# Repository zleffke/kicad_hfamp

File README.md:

# kicad_hfamp
Various KiCAD designs for HF Power Amplifiers

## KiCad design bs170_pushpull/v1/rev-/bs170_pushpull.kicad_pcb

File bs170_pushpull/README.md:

# bs170_pushpull

## Version 1
* Simple BS170 pushpull design
* utilizes two SMT BS170s, but added through hole pads for TO-92 testing.
* utilizes minicircuits baluns...ADTXXXXXX version
    * attempting to achieve wideband 'no tune' design.
    * not yet sure which impedance ratio to use
    * overlaid with through hole in order to test other baluns (hand made wirewound binocular...)
* No actual biasing circuit...planning to test offboard bias circuits.  Did include simple potentiometer based bias.
* Trying to achieve some amount of gain with a 5V drain voltage, most designs use 12V...
* Rev- design intended to test various configurations for biasing and to measure S-parameters.

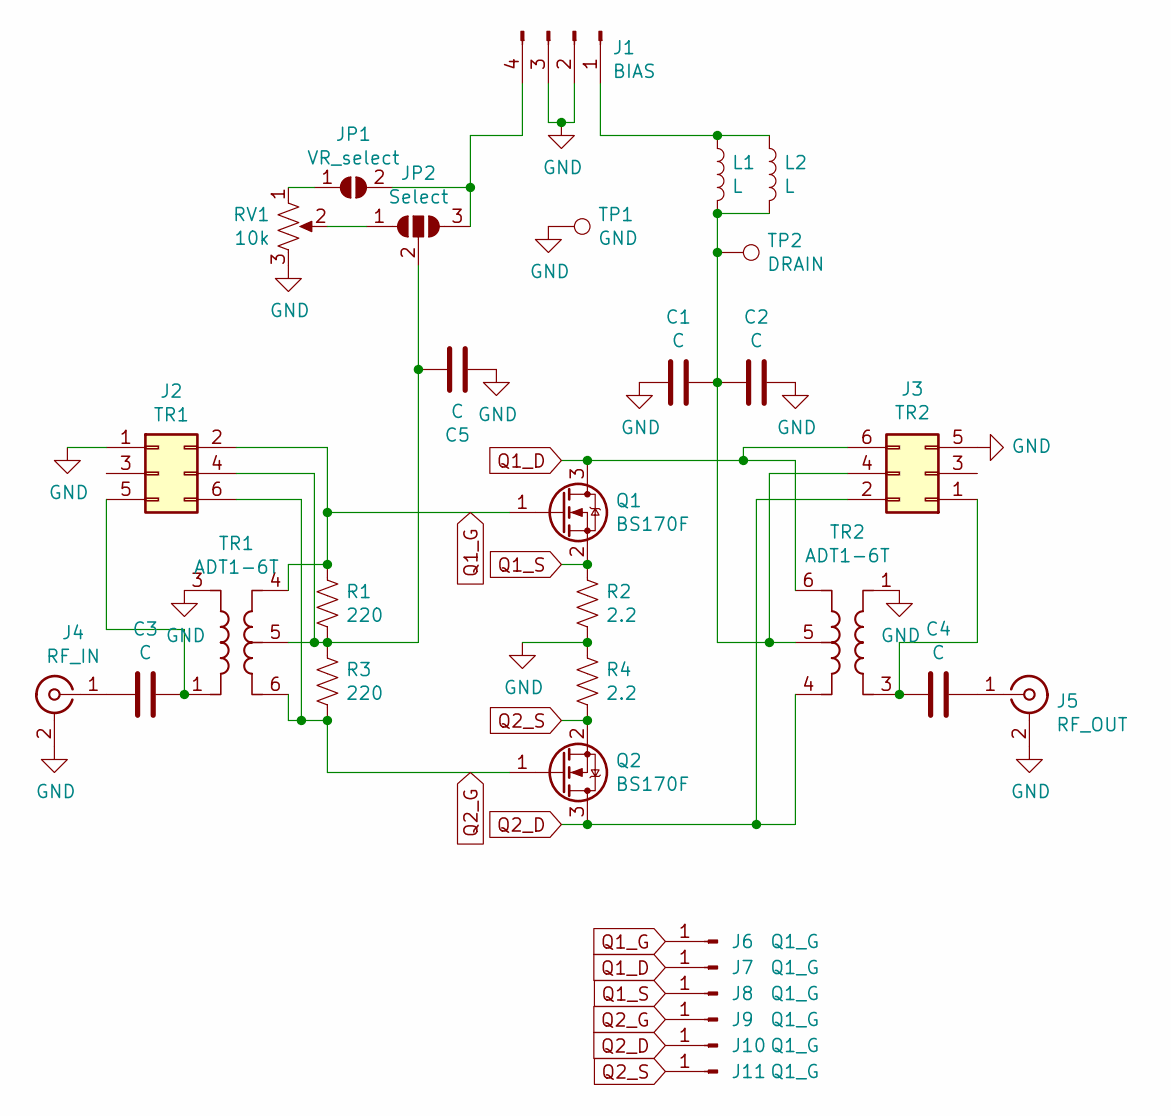
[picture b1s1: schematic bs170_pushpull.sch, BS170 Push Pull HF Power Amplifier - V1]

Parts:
C1, C2, C3, C4, C5: C; 0805
J1: BIAS; PinHeader_1x04_P2.54mm_Vertical
J2: TR1; PinHeader_2x03_P2.54mm_Vertical
J3: TR2; PinHeader_2x03_P2.54mm_Vertical
J4: RF_IN; SMA_Samtec_SMA-J-P-X-ST-EM1_EdgeMount
J5: RF_OUT; SMA_Samtec_SMA-J-P-X-ST-EM1_EdgeMount
J6, J7, J8, J9, J10, J11: Q1_G; PinHeader_1x01_P1.00mm_Vertical
JP1: VR_select; SolderJumper-2_P1.3mm_Open_RoundedPad1.0x1.5mm
JP2: Select; SolderJumper-3_P1.3mm_Open_RoundedPad1.0x1.5mm_NumberLabels
L1: L; PinHeader_1x02_P2.54mm_Vertical
L2: L; 0805
Q1, Q2: BS170F; SOT-23
R1, R3: 220; 0805
R2, R4: 2.2; 0805
RV1: 10k; Potentiometer_Bourns_3314G_Vertical
TP1: GND; TestPoint_Pad_D1.0mm
TP2: DRAIN; TestPoint_Pad_D1.0mm
TR1, TR2: ADT1-6T; Mini-Circuits_CD637_H5.23mm

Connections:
GND: C1.2, C2.1, C5.2, J1.2, J1.3, J2.1, J3.5, J4.2 (Ext), J5.2 (Ext), R2.2, R4.1, RV1.3, TP1.1, TR1.3, TR2.1
unnamed: C1.1, C2.2, J3.4, L1.2, L2.2, TP2.1, TR2.5
unnamed: C3.1, J2.5, TR1.1
unnamed: C3.2, J4.1 (In)
unnamed: C4.1, J5.1 (In)
unnamed: C4.2, J3.1, TR2.3
unnamed: C5.1, J2.4, JP2.2 (C), R1.2, R3.1, TR1.5
unnamed: J1.1, L1.1, L2.1
unnamed: J1.4, JP1.2 (B), JP2.3 (B)
unnamed: JP1.1 (A), RV1.1
unnamed: JP2.1 (A), RV1.2
Q1_D: J3.6, J7.1, Q1.3 (D), TR2.6
Q1_G: J2.2, J6.1, Q1.1 (G), R1.1, TR1.4
Q1_S: J8.1, Q1.2 (S), R2.1
Q2_D: J3.2, J10.1, Q2.3 (D), TR2.4
Q2_G: J2.6, J9.1, Q2.1 (G), R3.2, TR1.6
Q2_S: J11.1, Q2.2 (S), R4.2

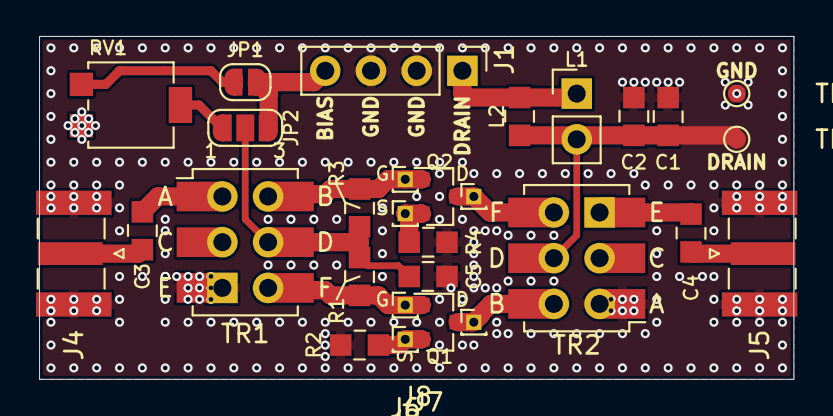
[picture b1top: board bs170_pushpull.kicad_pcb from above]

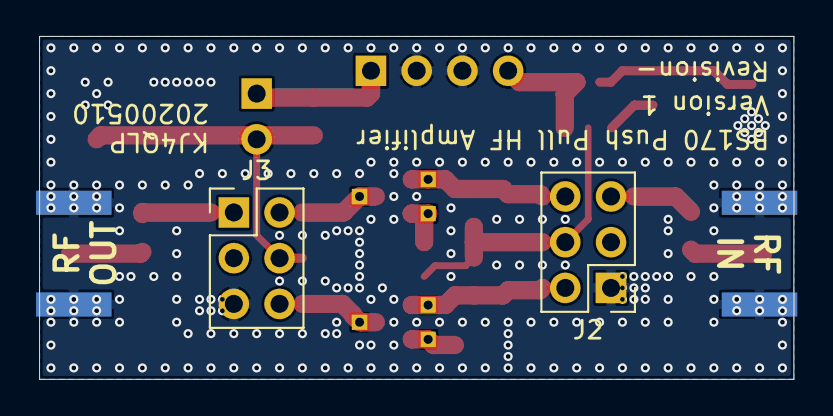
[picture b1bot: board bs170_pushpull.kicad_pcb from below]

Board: 2 copper layers, 41.9 x 19.0 mm, 31 parts (2 on the bottom side), 17 nets.

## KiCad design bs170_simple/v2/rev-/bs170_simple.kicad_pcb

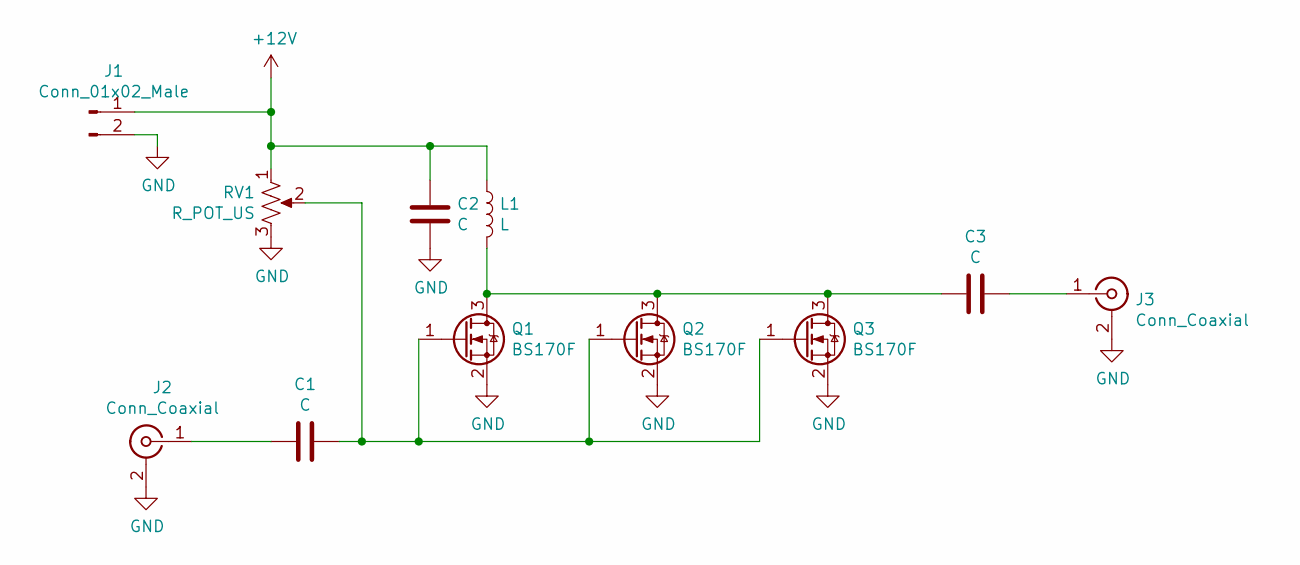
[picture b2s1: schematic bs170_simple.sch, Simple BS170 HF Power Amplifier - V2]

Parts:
C1, C2, C3: C; 0805
J1: Conn_01x02_Male; PinHeader_1x02_P2.54mm_Vertical
J2, J3: Conn_Coaxial; SMA_Samtec_SMA-J-P-X-ST-EM1_EdgeMount
L1: L; 0805
Q1, Q2, Q3: BS170F; SOT-23
RV1: R_POT_US; Potentiometer_Bourns_3314R-GM5_Vertical

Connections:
+12V: C2.2, J1.1, L1.1, RV1.1
GND: C2.1, J1.2, J2.2 (Ext), J3.2 (Ext), Q1.2 (S), Q2.2 (S), Q3.2 (S), RV1.3
unnamed: C1.1, Q1.1 (G), Q2.1 (G), Q3.1 (G), RV1.2
unnamed: C1.2, J2.1 (In)
unnamed: C3.1, J3.1 (In)
unnamed: C3.2, L1.2, Q1.3 (D), Q2.3 (D), Q3.3 (D)

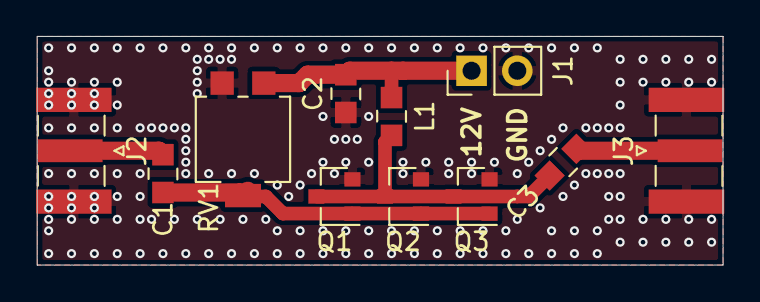
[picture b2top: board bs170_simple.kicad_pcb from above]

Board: 2 copper layers, 38.1 x 12.7 mm, 11 parts (0 on the bottom side), 6 nets.

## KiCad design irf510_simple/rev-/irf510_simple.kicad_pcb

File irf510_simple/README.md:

# irf510_simple
* Simple HF Power Amplifier, based on IRF510 MOSFET device.
* Should yield approx 5W output power.
* attempting to do this with SMT components, except for the IRF510.

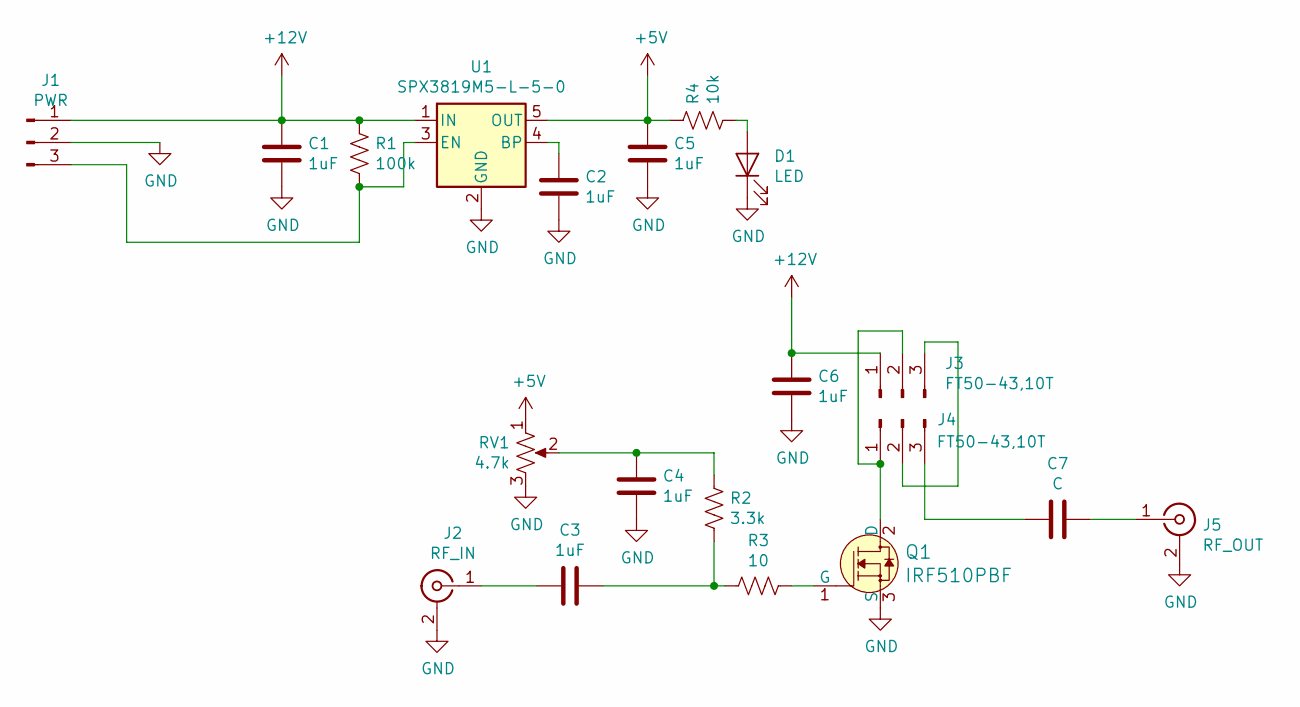
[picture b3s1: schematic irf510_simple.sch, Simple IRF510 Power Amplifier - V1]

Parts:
C1, C2, C3, C4, C5, C6: 1uF; 0805
C7: C; 0805
D1: LED; LED_0805_2012Metric
J1: PWR; PinSocket_1x03_P2.54mm_Vertical
J2: RF_IN; RF_SMA_BoardEdge_142-0701-801
J3, J4: FT50-43,10T; PinHeader_1x03_P2.54mm_Vertical
J5: RF_OUT; RF_SMA_BoardEdge_142-0701-801
Q1: IRF510PBF; TO-220-3; MPN IRF510PBF; Digi-Key_PN IRF510PBF-ND
R1: 100k; 0805
R2: 3.3k; 0805
R3: 10; 0805
R4: 10k; 0805
RV1: 4.7k; Trimpot_3.8mmx3.6mm_TC33X-2-103E
U1: SPX3819M5-L-5-0; SOT-23-5

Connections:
+5V: C5.2, R4.1, RV1.1, U1.5 (OUT)
+12V: C1.2, C6.2, J1.1, J3.1, R1.2, U1.1 (IN)
GND: C1.1, C2.1, C4.1, C5.1, C6.1, D1.1 (K), J1.2, J2.2 (Ext), J5.2 (Ext), Q1.3 (S), RV1.3, U1.2 (GND)
unnamed: C2.2, U1.4 (BP)
unnamed: C3.1, J2.1 (In)
unnamed: C3.2, R2.2, R3.2
unnamed: C4.2, R2.1, RV1.2
unnamed: C7.1, J5.1 (In)
unnamed: C7.2, J4.3
unnamed: D1.2 (A), R4.2
unnamed: J1.3, R1.1, U1.3 (EN)
unnamed: J3.2, J4.1, Q1.2 (D)
unnamed: J3.3, J4.2
unnamed: Q1.1 (G), R3.1

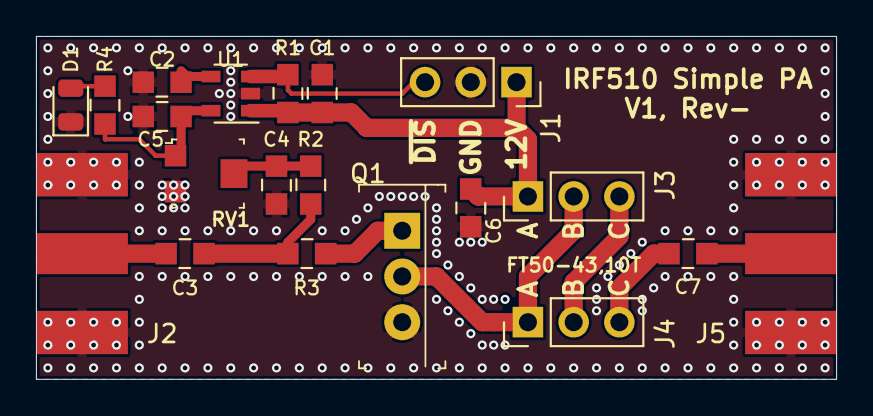
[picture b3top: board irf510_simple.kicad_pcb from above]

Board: 2 copper layers, 44.5 x 19.0 mm, 20 parts (0 on the bottom side), 14 nets.

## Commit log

2020-05-03 initial commit of first simple HF PA.
2020-05-12 adding rev- for simple BS170 pushpull desin. This commit submitted to oshpark on 20200512.
2020-05-12 simple layout for bs170 single ended design.
2020-05-12 fixed SMA connector footprint in v2, rev- design.
2020-05-25 fixed title on bottom silkscreen, added pdf of schematic.

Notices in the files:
bs170_pushpull/v1/rev-/bs170_pushpull.kicad_pcb:
License: CC BY 4.0
bs170_pushpull/v1/rev-/bs170_pushpull.sch:
creativecommons.org/licenses/by/4.0
